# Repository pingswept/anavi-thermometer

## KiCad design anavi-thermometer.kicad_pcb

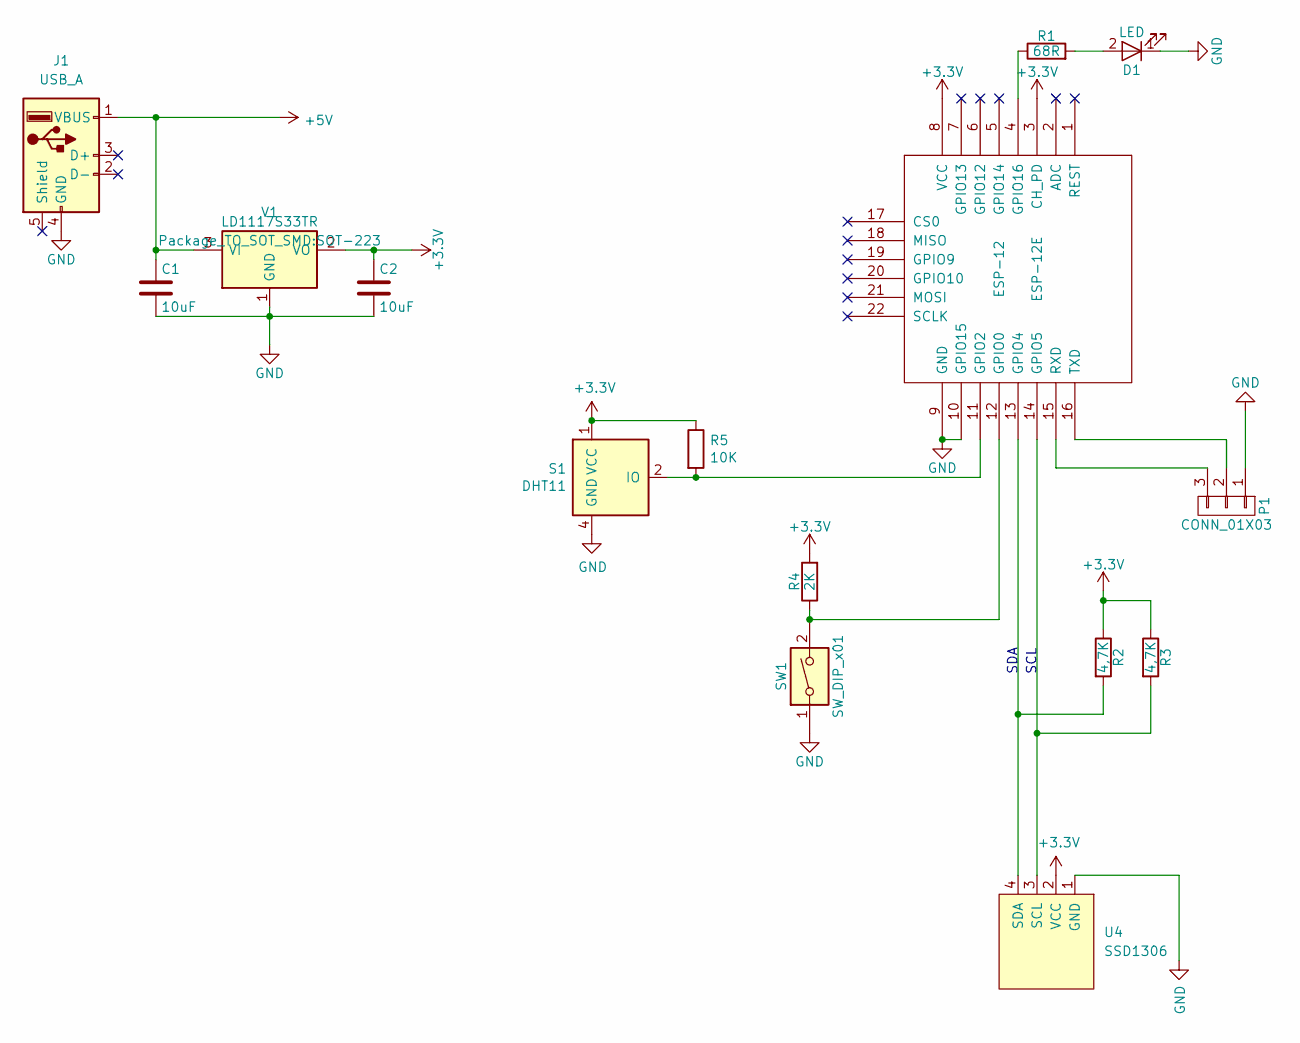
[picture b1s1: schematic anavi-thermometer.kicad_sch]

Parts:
C1, C2: 10uF; C_0805_2012Metric
D1: LED; LED_1206_3216Metric
ESP-12: ESP-12E; ESP-12E_SMD
J1: USB_A; USB_A_Plug_GCT_USB1061_Horizontal
P1: CONN_01X03; Pin_Header_Straight_1x03
R1: 68R; R_0603_1608Metric
R2, R3: 4,7K; R_0603_1608Metric
R4: 2K; R_0603_1608Metric
R5: 10K; R_0603_1608Metric
S1: DHT11; PinHeader_1x04_P2.54mm_Vertical
SW1: SW_DIP_x01; SW_PUSH_6mm_h4.3mm
U4: SSD1306; 128x64OLED
V1: LD1117S33TR; SOT-223

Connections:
+3V3: C2.1, ESP-12.3 (CH_PD), ESP-12.8 (VCC), R2.1, R3.1, R4.2, R5.1, S1.1 (VCC), U4.2 (VCC), V1.2 (VO)
+5V: C1.1, J1.1 (VBUS), V1.3 (VI)
GND: C1.2, C2.2, D1.1 (K), ESP-12.9 (GND), ESP-12.10 (GPIO15), J1.4 (GND), P1.1, S1.4 (GND), SW1.1, U4.1 (GND), V1.1 (GND)
unnamed: D1.2 (A), R1.2
unnamed: ESP-12.4 (GPIO16), R1.1
unnamed: ESP-12.11 (GPIO2), R5.2, S1.2 (IO)
unnamed: ESP-12.12 (GPIO0), R4.1, SW1.2
unnamed: ESP-12.13 (GPIO4), R2.2, U4.4 (SDA)
unnamed: ESP-12.14 (GPIO5), R3.2, U4.3 (SCL)
unnamed: ESP-12.15 (RXD), P1.3
unnamed: ESP-12.16 (TXD), P1.2

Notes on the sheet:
SCL
SDA

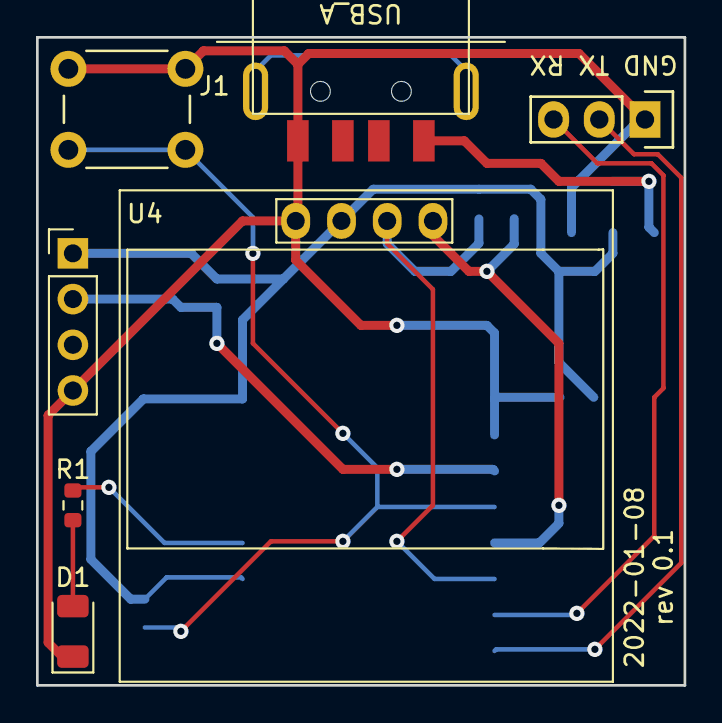
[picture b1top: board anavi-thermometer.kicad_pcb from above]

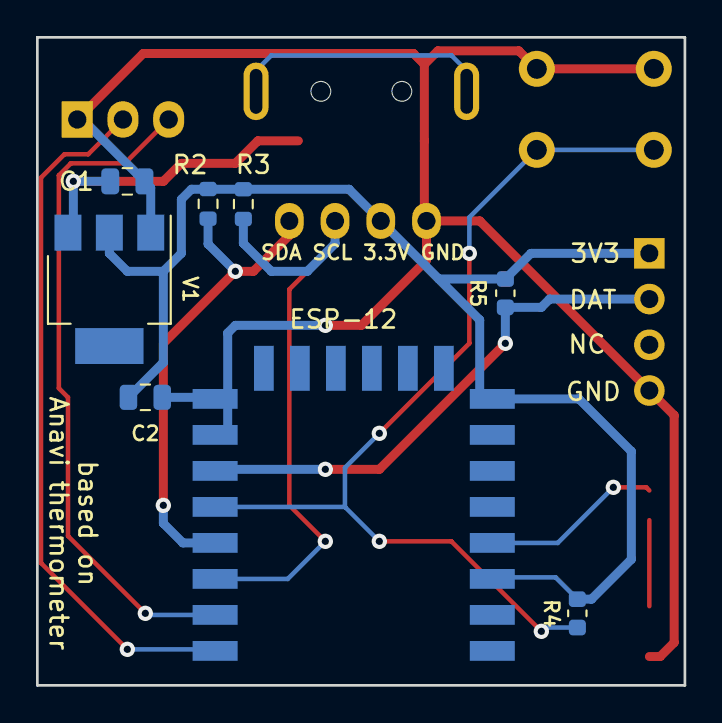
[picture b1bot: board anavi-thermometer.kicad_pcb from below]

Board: 2 copper layers, 36.0 x 36.0 mm, 15 parts (8 on the bottom side), 11 nets.

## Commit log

2022-01-08 update to Kicad 6
2022-01-09 rev 0.1
